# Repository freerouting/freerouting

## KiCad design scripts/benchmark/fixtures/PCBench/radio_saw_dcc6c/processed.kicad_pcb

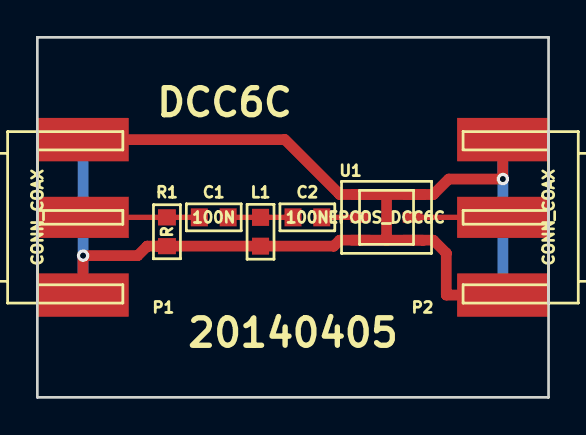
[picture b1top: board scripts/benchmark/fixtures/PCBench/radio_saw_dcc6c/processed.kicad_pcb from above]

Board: 4 copper layers, 28.4 x 20.0 mm, 7 parts (0 on the bottom side), 5 nets.

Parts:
C1, C2: 100N; IPC_CAPC1608X95N
L1: L; IPC_INDC1608X95N
P1, P2: CONN_COAX; EMERSON_142-0701-801
R1: R; IPC_RESC1608X55N
U1: EPCOS_DCC6C

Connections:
GND: L1.2, P1.2, P2.2, R1.2, U1.1, U1.3, U1.4, U1.6
unnamed: C1.1, P1.1, R1.1
unnamed: C1.2, C2.1, L1.1
unnamed: C2.2, U1.2
unnamed: P2.1, U1.5

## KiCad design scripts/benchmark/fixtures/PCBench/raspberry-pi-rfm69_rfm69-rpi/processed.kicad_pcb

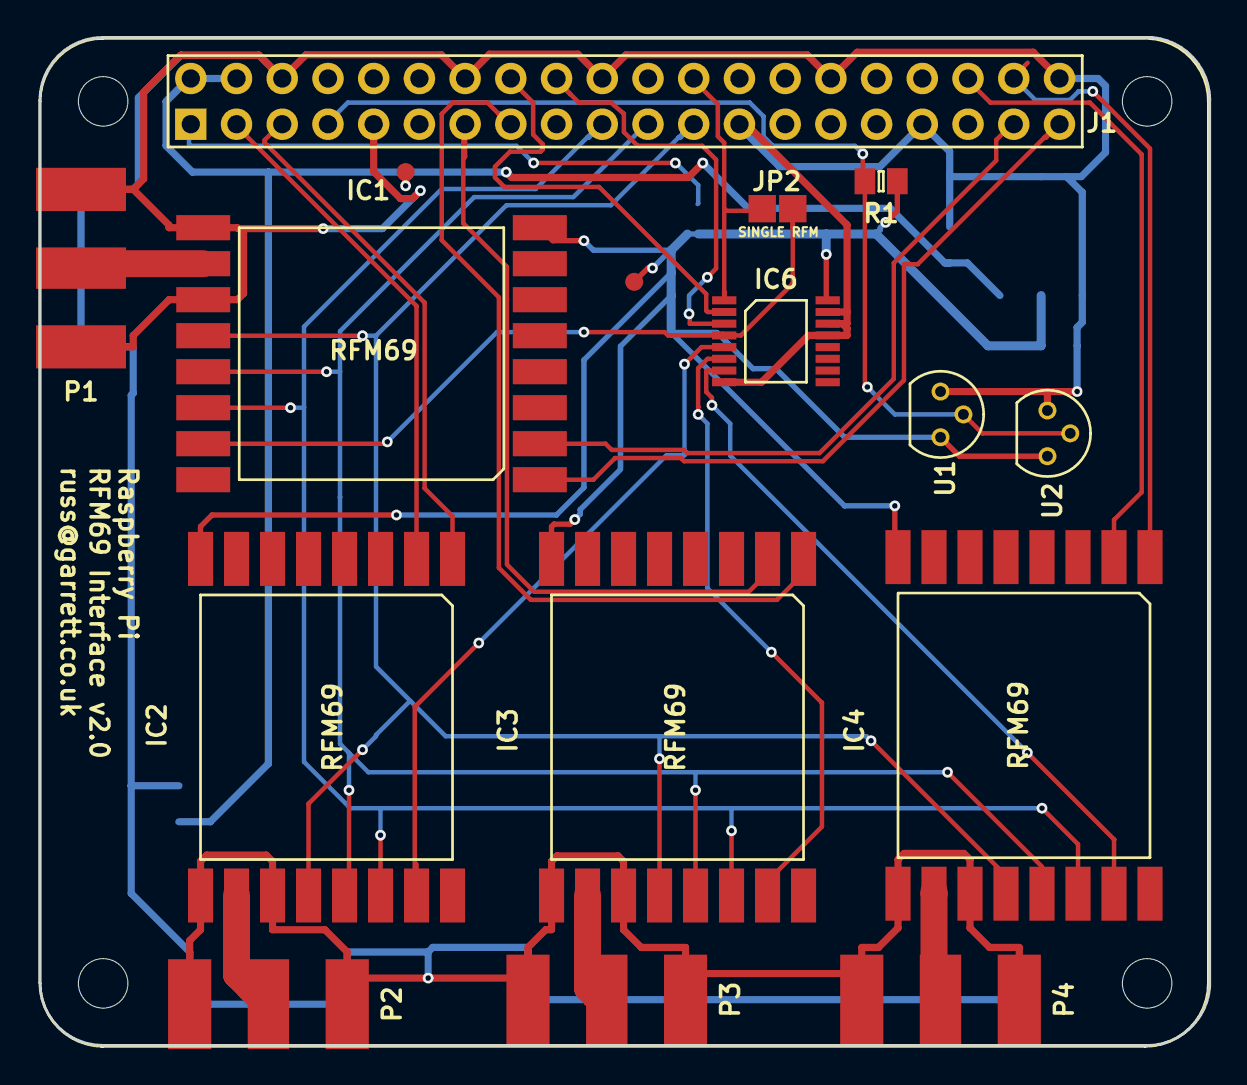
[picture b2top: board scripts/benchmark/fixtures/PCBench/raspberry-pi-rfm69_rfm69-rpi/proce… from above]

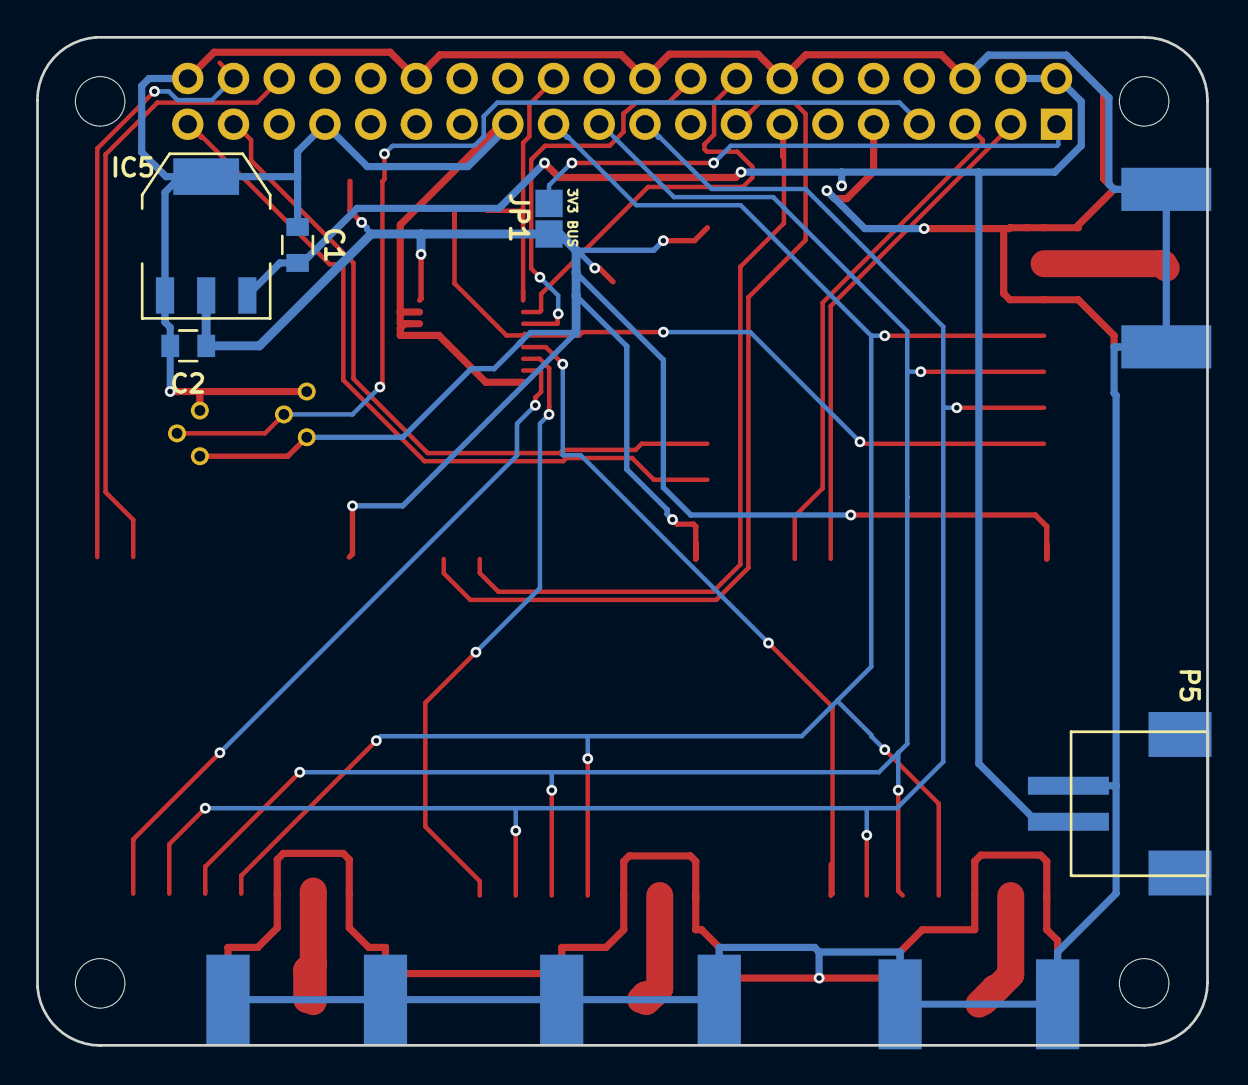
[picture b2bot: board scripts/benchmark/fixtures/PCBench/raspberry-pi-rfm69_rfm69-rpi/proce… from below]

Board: 2 copper layers, 65.0 x 56.0 mm, 21 parts (5 on the bottom side), 27 nets.

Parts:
C1, C2: 10uF; C_0805
IC1, IC2, IC3, IC4: RFM69
IC5: NCP1117; SOT-223
IC6: 74HC139; TSSOP-16
J1: RPi_GPIO; raspberrypi2
JP1: 3V3 BUS; TESTPT
JP2: SINGLE RFM; TESTPT
P1, P2, P3, P4: COAX; SMA-EDGE
P5: POWER; JST-PH-SM4-2
R1: 4k7; 0805
TP1, TP2: TESTPAD
U1, U2: 1-Wire; TO-92_Molded_Narrow

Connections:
+3V3: C2.1, IC1.8, IC2.8, IC3.8, IC4.8, IC5.2, IC6.16, JP1.1, R1.1, TP2.1, U1.3, U2.3
+5V: C1.1, IC5.3, J1.2, J1.4, P5.1, TP1.1
/3V3_SUPP: J1.1, JP1.2
/ANT_1: IC1.10, P1.1
/ANT_2: IC2.10, P2.1
/ANT_3: IC3.10, P3.1
/ANT_4: IC4.10, P4.1
Earth: C1.2, C2.2, IC1.9, IC1.11, IC2.9, IC2.11, IC3.9, IC3.11, IC4.9, IC4.11, IC5.1, IC5.4, IC6.8, IC6.13, IC6.14, IC6.15, J1.6, J1.9, J1.14, J1.20, J1.25, J1.30, J1.34, J1.39, P1.2, P2.2, P3.2, P4.2, P5.2, U1.1, U2.1
INT1: IC1.2, J1.38
INT2: IC2.2, J1.3
INT3: IC3.2, J1.13
INT4: IC4.2, J1.35
MISO: IC1.13, IC2.13, IC3.13, IC4.13, J1.21
MOSI: IC1.14, IC2.14, IC3.14, IC4.14, J1.19
NSS: IC6.1, J1.24, JP2.1
NSS1: IC1.15, IC6.4, JP2.2
NSS2: IC2.15, IC6.5
NSS3: IC3.15, IC6.6
NSS4: IC4.15, IC6.7
unnamed: IC6.2, J1.16
unnamed: IC6.3, J1.18
ONEWIRE: J1.7, R1.2, U1.2, U2.2
RESET1: IC1.1, J1.40
RESET2: IC2.1, J1.5
RESET3: IC3.1, J1.15
RESET4: IC4.1, J1.37
SCK: IC1.12, IC2.12, IC3.12, IC4.12, J1.23

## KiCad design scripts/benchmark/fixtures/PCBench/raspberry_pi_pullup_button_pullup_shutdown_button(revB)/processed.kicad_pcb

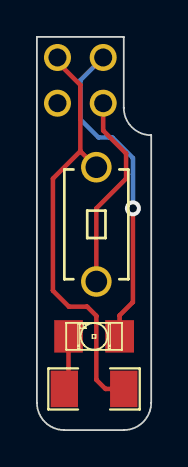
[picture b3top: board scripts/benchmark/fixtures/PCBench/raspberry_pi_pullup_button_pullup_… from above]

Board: 2 copper layers, 6.4 x 21.8 mm, 4 parts (0 on the bottom side), 4 nets.

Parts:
D1: LED; LED-1206
R1: R; SM1206
SW1: SW_PUSH; button_single_custom
U1: PI_SHUTDOWN; pi_shutdown_4pin

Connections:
unnamed: D1.1, U1.16
unnamed: R1.1, SW1.1, U1.14
unnamed: SW1.2, U1.15
unnamed: D1.2, R1.2
